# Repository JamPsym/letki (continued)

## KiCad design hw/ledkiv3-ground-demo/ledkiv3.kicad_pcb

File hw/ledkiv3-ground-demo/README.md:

# Live ground-repair demo

This working copy comes from `archive/hw/ledkiv3/`. It demonstrates repairing the disconnected C1/C3 ground sections, using the official KiCad IPC API. It is a demonstration layout, not a fabrication release or a renamed v4 revision.

The repair adds one through GND via at (45.076, 78.000) mm, with 0.5 mm copper diameter and 0.3 mm drill, and a 0.25 mm front-layer trace to the existing ground via at (45.711, 67.356) mm. The route goes around existing copper toward the left edge. This intentionally conservative route is longer than an optimized redesign.

The prechecked repair eliminated the missing ground connection without adding clearance, short, or track-width violations. Other existing DRC findings remain; no fabrication exports were generated. Local reports are under `build/hardware/v3-ground-audit/`.

## Replay in KiCad

The local `.tools/kicad-api/` environment contains `kicad-python==0.8.0`. KiCad's API server has been enabled in Preferences. Open this copy with the existing desktop launcher:

```sh
pcbnew hw/ledkiv3-ground-demo/ledkiv3.kicad_pcb
```

Immediately after the agent's live edit, Ctrl+Z undoes the grouped repair. Save the unrepaired demo before replaying (undo history does not survive closing the editor). Then run:

```sh
.tools/kicad-api/bin/python scripts/pcb_ground_demo.py
```

The script shows the new via for eight seconds, adds the trace, refills zones, selects the repair and saves the demo. It checks the open project path and refuses to add a duplicate via. It does not edit the archive. After undoing, refill zones to update connectivity.

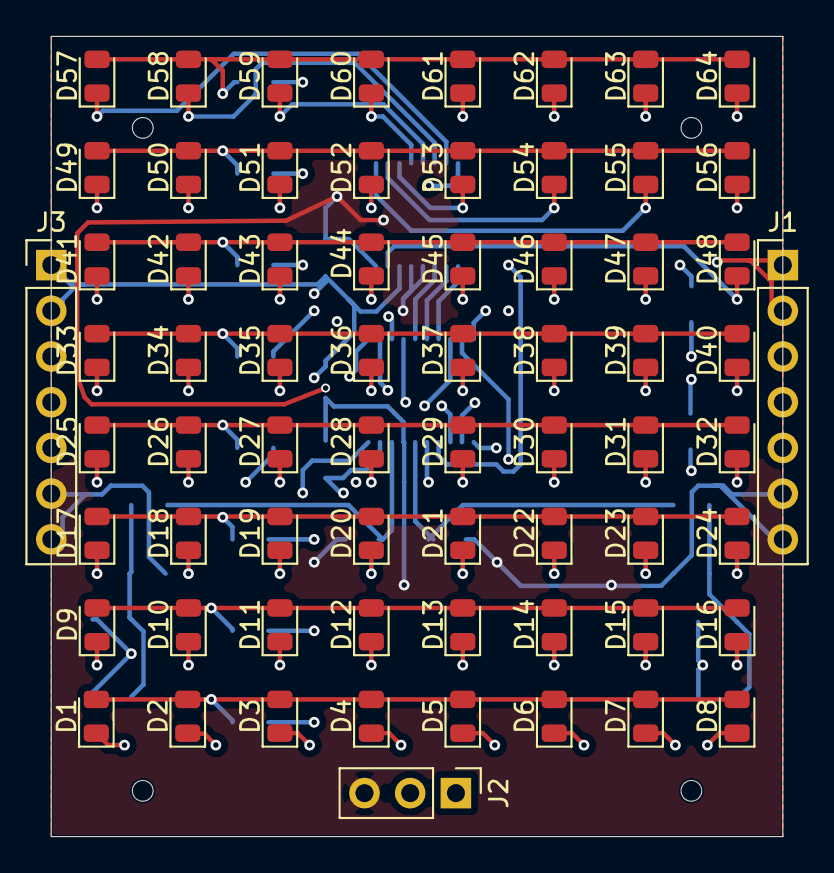
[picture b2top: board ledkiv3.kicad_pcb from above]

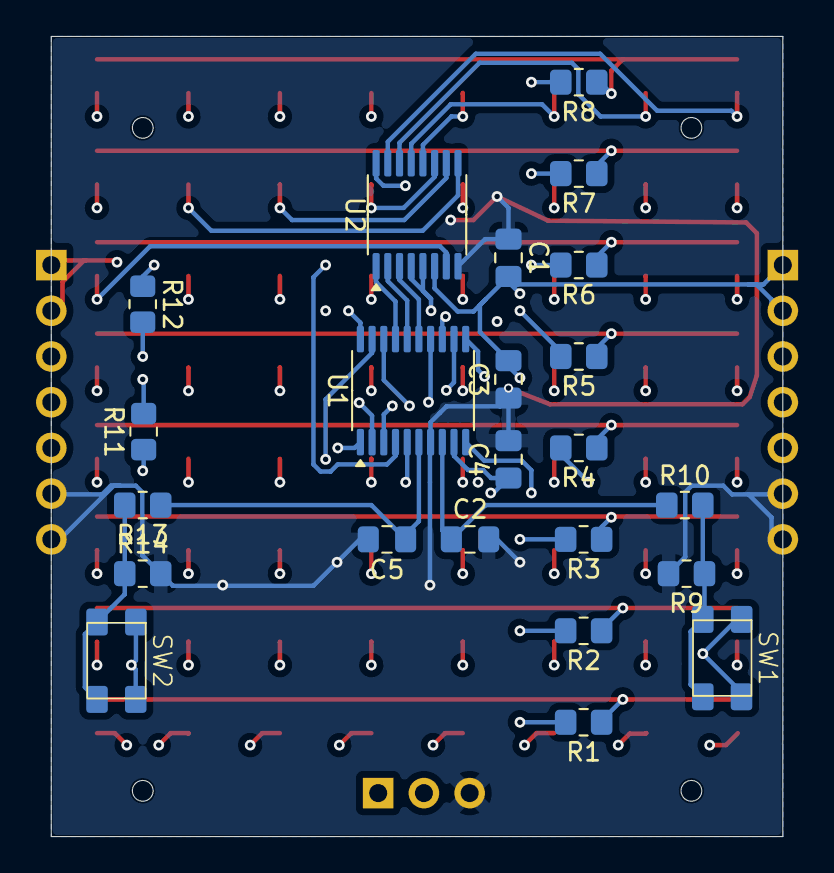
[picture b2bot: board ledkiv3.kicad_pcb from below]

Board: 4 copper layers, 40.6 x 44.4 mm, 90 parts (23 on the bottom side), 38 nets.

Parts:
C1, C3: 0.1 uF; C_0805_2012Metric_Pad1.18x1.45mm_HandSolder
C2, C5: 0.1uF; C_0805_2012Metric_Pad1.18x1.45mm_HandSolder
C4: 10 uF; C_0805_2012Metric_Pad1.18x1.45mm_HandSolder
D1, D2, D3, D4, D5, D6, D7, D8, D9, D10, D11, D12, D13, D14, D15, D16, D17, D18, D19, D20, D21, D22, D23, D24, D25, D26, D27, D28, D29, D30, D31, D32, D33, D34, D35, D36, D37, D38, D39, D40, D41, D42, D43, D44, D45, D46, D47, D48, D49, D50, D51, D52, D53, D54, D55, D56, D57, D58, D59, D60, D61, D62, D63, D64: LED; LED_0805_2012Metric
J1: Right Conn; PinHeader_1x07_P2.54mm_Vertical
J2: Conn_01x03; PinHeader_1x03_P2.54mm_Vertical
J3: Left Conn; PinHeader_1x07_P2.54mm_Vertical
R1, R2, R3, R4, R5, R6, R7, R8: R; R_0805_2012Metric_Pad1.20x1.40mm_HandSolder
R9, R10, R13, R14: 10K; R_0805_2012Metric_Pad1.20x1.40mm_HandSolder
R11, R12: 4.7k; R_0805_2012Metric_Pad1.20x1.40mm_HandSolder
SW1, SW2: SW_Push; SW_tactile_TS-1089S
U1: CH32V003FxPx; TSSOP-20_4.4x6.5mm_P0.65mm
U2: 74HC138; TSSOP-16_4.4x5mm_P0.65mm

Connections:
/BUTT1: C2.1, R10.1, U1.8 (PD0)
/BUTT2: C5.1, R13.1, U1.6 (PA2)
/D1: R1.2, U1.19 (PD2)
/D2: R2.2, U1.5 (PA1)
/D3: R3.2, U1.13 (PC3)
/D4: R4.2, U1.14 (PC4)
/D5: R5.2, U1.1 (PD4)
/D6: R6.2, U1.20 (PD3)
/D7: R7.2, U1.10 (PC0)
/D8: R8.2, U1.4 (PD7)
/S1: D1.1 (K), D9.1 (K), D17.1 (K), D25.1 (K), D33.1 (K), D41.1 (K), D49.1 (K), D57.1 (K), U2.15 (~Y0)
/S2: D2.1 (K), D10.1 (K), D18.1 (K), D26.1 (K), D34.1 (K), D42.1 (K), D50.1 (K), D58.1 (K), U2.14 (~Y1)
/S3: D3.1 (K), D11.1 (K), D19.1 (K), D27.1 (K), D35.1 (K), D43.1 (K), D51.1 (K), D59.1 (K), U2.13 (~Y2)
/S4: D4.1 (K), D12.1 (K), D20.1 (K), D28.1 (K), D36.1 (K), D44.1 (K), D52.1 (K), D60.1 (K), U2.12 (~Y3)
/S5: D5.1 (K), D13.1 (K), D21.1 (K), D29.1 (K), D37.1 (K), D45.1 (K), D53.1 (K), D61.1 (K), U2.11 (~Y4)
/S6: D6.1 (K), D14.1 (K), D22.1 (K), D30.1 (K), D38.1 (K), D46.1 (K), D54.1 (K), D62.1 (K), U2.10 (~Y5)
/S7: D7.1 (K), D15.1 (K), D23.1 (K), D31.1 (K), D39.1 (K), D47.1 (K), D55.1 (K), D63.1 (K), U2.9 (~Y6)
/S8: D8.1 (K), D16.1 (K), D24.1 (K), D32.1 (K), D40.1 (K), D48.1 (K), D56.1 (K), D64.1 (K), U2.7 (~Y7)
/SCL: J1.4, J3.4, R11.2, U1.12 (PC2)
/SDA: J1.3, J3.3, R12.2, U1.11 (PC1)
/SWDIO: J2.2, U1.18 (PD1)
/URX: J3.5, U1.3 (PD6)
/UTX: J1.5, U1.2 (PD5)
GND: C1.1, C2.2, C3.1, C4.2, C5.2, J1.6, J1.7, J2.3, J3.6, J3.7, R9.2, R14.2, U1.7 (VSS), U2.4 (~E0), U2.5 (~E1), U2.8 (GND)
unnamed: D1.2 (A), D2.2 (A), D3.2 (A), D4.2 (A), D5.2 (A), D6.2 (A), D7.2 (A), D8.2 (A), R1.1
unnamed: D9.2 (A), D10.2 (A), D11.2 (A), D12.2 (A), D13.2 (A), D14.2 (A), D15.2 (A), D16.2 (A), R2.1
unnamed: D17.2 (A), D18.2 (A), D19.2 (A), D20.2 (A), D21.2 (A), D22.2 (A), D23.2 (A), D24.2 (A), R3.1
unnamed: D25.2 (A), D26.2 (A), D27.2 (A), D28.2 (A), D29.2 (A), D30.2 (A), D31.2 (A), D32.2 (A), R4.1
unnamed: D33.2 (A), D34.2 (A), D35.2 (A), D36.2 (A), D37.2 (A), D38.2 (A), D39.2 (A), D40.2 (A), R5.1
unnamed: D41.2 (A), D42.2 (A), D43.2 (A), D44.2 (A), D45.2 (A), D46.2 (A), D47.2 (A), D48.2 (A), R6.1
unnamed: D49.2 (A), D50.2 (A), D51.2 (A), D52.2 (A), D53.2 (A), D54.2 (A), D55.2 (A), D56.2 (A), R7.1
unnamed: D57.2 (A), D58.2 (A), D59.2 (A), D60.2 (A), D61.2 (A), D62.2 (A), D63.2 (A), D64.2 (A), R8.1
unnamed: R9.1, R10.2, SW1.2
unnamed: R13.2, R14.1, SW2.2
unnamed: U1.15 (PC5), U2.3 (A2)
unnamed: U1.16 (PC6), U2.2 (A1)
unnamed: U1.17 (PC7), U2.1 (A0)
VCC: C1.2, C3.2, C4.1, J1.1, J1.2, J2.1, J3.1, J3.2, R11.1, R12.1, SW1.1, SW2.1, U1.9 (VDD), U2.6 (E2), U2.16 (VCC)

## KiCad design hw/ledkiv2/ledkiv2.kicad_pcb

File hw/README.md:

# Hardware projects

Each maintained board uses the same basic layout: open its KiCad project directly
in `hw/<board>/`; local libraries and models stay beside it, mechanical source
belongs in `mechanics/` when present, and generated handoffs go in `exports/`.
Keep superseded board-specific designs in `archive/hw/`, raw experiments in
`build/hardware/`, and reusable research in `~/electronics/notes/`.

| Folder | Role | Open |
| --- | --- | --- |
| [ledkiv3.2](ledkiv3.2/README.md) | Accepted main v3.2 after manual edits and trace cleanup; frozen milestone saved | [KiCad](ledkiv3.2/ledkiv3_2.kicad_pro) |
| [ledkiv3.1](ledkiv3.1/README.md) | Accepted v3.1 baseline; frozen source/package saved, physical qualification pending | [KiCad](ledkiv3.1/ledkiv3_1.kicad_pro) |
| [ledkiv4](ledkiv4/README.md) | Preserved v4 prototype candidate | [KiCad](ledkiv4/ledkiv4.kicad_pro) |
| [ledkiv4.1](ledkiv4.1/README.md) | Selected earlier purchase baseline; see current-state and assembly substitutions | [KiCad](ledkiv4.1/ledkiv4_1.kicad_pro) |
| [ledkiv3-ground-demo](ledkiv3-ground-demo/README.md) | Live editable repair demonstration; not a fabrication candidate | [PCB](ledkiv3-ground-demo/ledkiv3.kicad_pcb) |

The original v3 and older revisions are archived. V3.1 circuit-study schematics
are in [the dated archive](../archive/hw/ledkiv3.1-studies-20261015/README.txt).
Automatic `.history/`, editor state and existing frozen export ZIPs are retained.
Do not regenerate CAD or an uploaded package as part of folder maintenance.

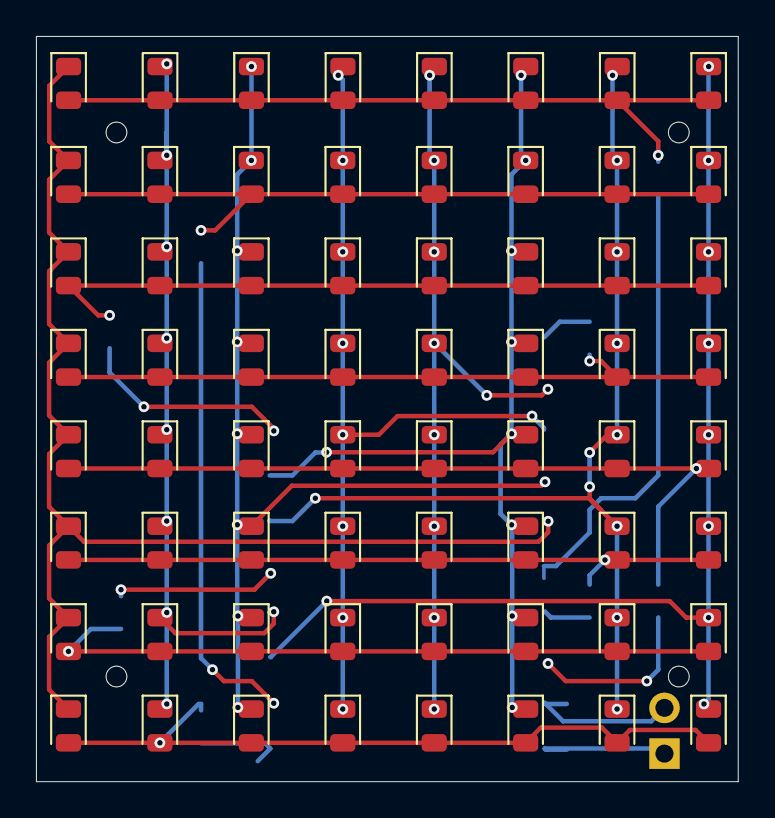
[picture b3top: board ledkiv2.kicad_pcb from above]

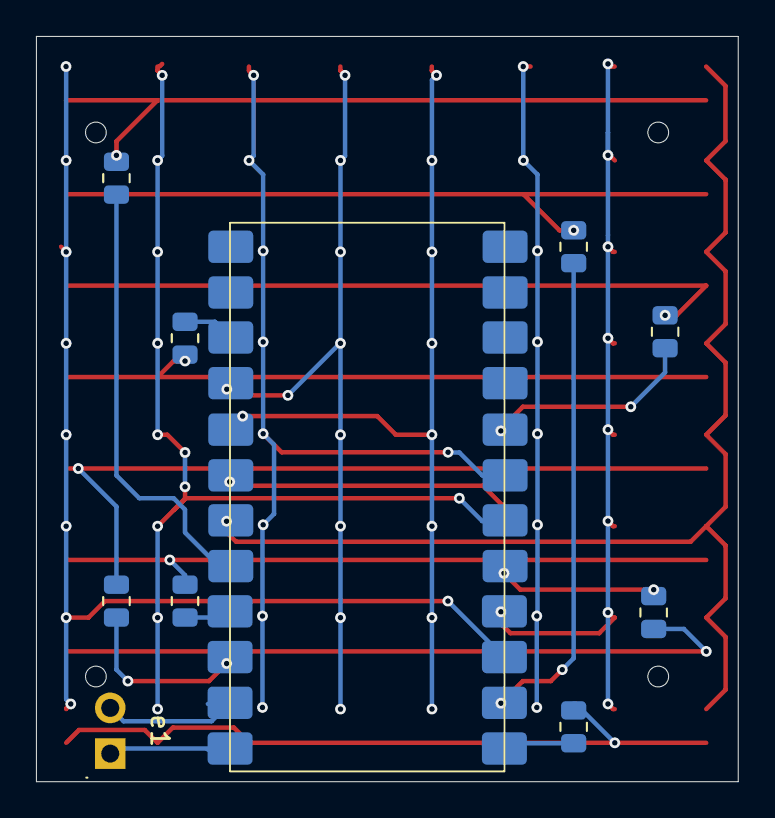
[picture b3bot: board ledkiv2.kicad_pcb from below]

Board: 2 copper layers, 39.0 x 41.4 mm, 74 parts (10 on the bottom side), 26 nets.

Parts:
D1, D2, D3, D4, D5, D6, D7, D8, D9, D10, D11, D12, D13, D14, D15, D16, D17, D18, D19, D20, D21, D22, D23, D24, D25, D26, D27, D28, D29, D30, D31, D32, D33, D34, D35, D36, D37, D38, D39, D40, D41, D42, D43, D44, D45, D46, D47, D48, D49, D50, D51, D52, D53, D54, D55, D56, D57, D58, D59, D60, D61, D62, D63, D64: LED; LED_0805_2012Metric
J1: Conn_02x12_Counter_Clockwise; ch32v003weact_SolderPad_15.24mm
R1, R2, R3, R4, R5, R6, R7, R8: R; R_0805_2012Metric
e1: Conn_01x02; PinSocket_2x01_P2.54mm_Vertical

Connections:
unnamed: D1.2 (A), D9.2 (A), D17.2 (A), D18.2 (A), D33.2 (A), D34.2 (A), D35.2 (A), D36.2 (A), R1.1
unnamed: D1.1 (K), D2.1 (K), D3.1 (K), D4.1 (K), D5.1 (K), D6.1 (K), D7.1 (K), D8.1 (K), J1.7 (D1)
unnamed: D2.2 (A), D10.2 (A), D19.2 (A), D20.2 (A), D37.2 (A), D38.2 (A), D39.2 (A), D40.2 (A), R2.1
unnamed: D9.1 (K), D10.1 (K), D11.1 (K), D12.1 (K), D13.1 (K), D14.1 (K), D15.1 (K), D16.1 (K), J1.16 (D0)
unnamed: D3.2 (A), D11.2 (A), D21.2 (A), D22.2 (A), D41.2 (A), D42.2 (A), D43.2 (A), D44.2 (A), R3.1
unnamed: D4.2 (A), D12.2 (A), D23.2 (A), D24.2 (A), D45.2 (A), D46.2 (A), D47.2 (A), D48.2 (A), R4.1
unnamed: D5.2 (A), D13.2 (A), D25.2 (A), D26.2 (A), D49.2 (A), D50.2 (A), D51.2 (A), D52.2 (A), R5.1
unnamed: D6.2 (A), D14.2 (A), D27.2 (A), D28.2 (A), D53.2 (A), D54.2 (A), D55.2 (A), D56.2 (A), R6.1
unnamed: D7.2 (A), D15.2 (A), D29.2 (A), D30.2 (A), D57.2 (A), D58.2 (A), D59.2 (A), D60.2 (A), R7.1
unnamed: D8.2 (A), D16.2 (A), D31.2 (A), D32.2 (A), D61.2 (A), D62.2 (A), D63.2 (A), D64.2 (A), R8.1
unnamed: D17.1 (K), D19.1 (K), D21.1 (K), D23.1 (K), D25.1 (K), D27.1 (K), D29.1 (K), D31.1 (K), J1.6 (C7)
unnamed: D18.1 (K), D20.1 (K), D22.1 (K), D24.1 (K), D26.1 (K), D28.1 (K), D30.1 (K), D32.1 (K), J1.5 (C6)
unnamed: D33.1 (K), D37.1 (K), D41.1 (K), D45.1 (K), D49.1 (K), D53.1 (K), D57.1 (K), D61.1 (K), J1.4 (C5)
unnamed: D34.1 (K), D38.1 (K), D42.1 (K), D46.1 (K), D50.1 (K), D54.1 (K), D58.1 (K), D62.1 (K), J1.19 (C2)
unnamed: D35.1 (K), D39.1 (K), D43.1 (K), D47.1 (K), D51.1 (K), D55.1 (K), D59.1 (K), D63.1 (K), J1.18 (C1)
unnamed: D36.1 (K), D40.1 (K), D44.1 (K), D48.1 (K), D52.1 (K), D56.1 (K), D60.1 (K), D64.1 (K), J1.15 (A2)
unnamed: J1.14 (A1), R2.2
unnamed: J1.17 (C0), R7.2
unnamed: J1.20 (C3), R3.2
unnamed: J1.3 (C4), R4.2
unnamed: J1.8 (D2), R1.2
unnamed: J1.9 (D3), R6.2
unnamed: J1.10 (D4), R5.2
unnamed: J1.11 (D5), e1.2 (tx-PD5)
unnamed: J1.12 (D6), e1.1 (rx-PD6)
unnamed: J1.13 (D7), R8.2

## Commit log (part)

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2025-10-11 Refactor render loops
2025-10-11 Project files
2025-10-11 Initial PWM configuration for matrix display
2025-10-16 Reorganize project layout and clean artifacts
2025-10-16 Fix MounRiver builder path after project move
2025-10-16 clean up kicad files
2025-11-01 dyfuzorek
2025-11-03 ja sem defuzorek v3
